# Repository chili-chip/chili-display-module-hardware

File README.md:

# chili-display-module

KiCad 10 project for the **chilichip console display module**. The module is a small board with the panel's FPC connector and backlight switch, soldered to the main board by castellated pads on its left and right edges. The panel itself is glued or screwed to the console frame, and its flex tail plugs into the module.

The console has one screen: the 2.0" IPS TFT, 320 × 240, mounted sideways. The 1.5" OLED and 1.44" TFT modules were dropped on 2026-11-27 (they are in the git history up to [#2](https://github.com/chili-chip/chili-display-module-hardware/pull/2)).

All parts are on the module's top side, so its bottom is flat. The module lies flat on the main board and is hand soldered by its edge pads, like a Raspberry Pi Pico.

Status: **schematic and PCB done, autorouted.** 28 × 22 mm. ERC and DRC are clean (DRC with schematic parity). Not ordered or tested.

| Folder | Panel | Controller | Extra parts on the module |
|---|---|---|---|
| [`tft/`](tft/) | [EastRising ER-TFT020-3](https://www.buydisplay.com/2-inch-240x320-ips-tft-lcd-display-with-connector-fpc), 2.0" IPS 320 × 240, 14-pin 0.5 mm FPC | ST7789 | Backlight switch |

| Top | Bottom |
|:---:|:---:|
|  |  |

## Board

| | |
|---|---|
| Outline | 28 × 22 mm, 1.6 mm FR-4, two layers |
| Edge pads | 8 castellated half-holes, 2.54 mm pitch, 1 mm drill: 4 on the left edge (J1), 4 on the right edge (J3) |
| Panel | Not on the module. It is mounted on the frame; its FPC tail folds back under the panel and plugs into J2 |
| Parts side | Top. The bottom is flat and lies on the main board. One-sided JLCPCB assembly |
| FPC connector | J2, Hirose FH12-14S (0.5 mm, 0.3 mm FPC), top side, opening at the bottom edge, centred at x = 8.5 mm (off centre, see below) |
| GND | Poured on both layers |
| Test pads | 8 bare 1 mm pads on the top side, labelled on the silkscreen (see below). No assembly needed |

Coordinates are top view, origin at the module's top-left corner.

### Edge pads

| Pad | Edge, y (mm) | Net | RP2350 GPIO |
|---|---|---|---|
| J1.1 | Left, 14.81 | 3V3 | |
| J1.2 | Left, 12.27 | GND | |
| J1.3 | Left, 9.73 | `DISP_DIN` | GP27 |
| J1.4 | Left, 7.19 | `DISP_CLK` | GP26 |
| J3.1 | Right, 7.19 | `DISP_CS` | GP28 |
| J3.2 | Right, 9.73 | `DISP_DC` | GP22 |
| J3.3 | Right, 12.27 | `DISP_RST` | GP21 |
| J3.4 | Right, 14.81 | GND | |

The signals and GPIOs are the same as the old Waveshare module, so the firmware pin map doesn't change.

### Test pads

8 test pads on the top side, for probing during bring-up before the panel goes on. They are bare copper, so they add no parts and no cost.

| Pad | Net |
|---|---|
| TP1 | 3V3 |
| TP2 | GND |
| TP3 | `DISP_DIN` |
| TP4 | `DISP_CLK` |
| TP5 | `DISP_CS` |
| TP6 | `DISP_DC` |
| TP7 | `DISP_RST` |
| TP8 | BL: backlight cathode (`LED_K`) |

### Main board footprint

[`chili-display-module.pretty/ChiliDisplayModule_Host.kicad_mod`](chili-display-module.pretty/ChiliDisplayModule_Host.kicad_mod) is the footprint for the main board. It has the 8 pads (numbered 1–8 in the order of the table above) and the module outline on the silkscreen.

```
      0                                28   (mm)
   0  +---------------------------------+   module outline
      |                                 |
     pad                               pad
     pad   keep parts and bare copper  pad   pads stick out 1.6 mm
     pad   out from under the module   pad   past each side edge
     pad                               pad
      |                                 |
  22  +---------------------------------+
```

| | |
|---|---|
| Host pads | 2.6 × 1.6 mm, centred 0.3 mm outside the module edge, so the solder fillet forms on the edge |
| Under the module | No parts and no bare copper. Tracks and tented vias are fine |
| Height above the main board | 3.6 mm: 1.6 mm board plus the FH12 connector (2.0 mm), the tallest part. The panel sits on the frame above |

### Backlight follows `DISP_RST`

The console has no free GPIO, so the reset line is also the backlight switch:

| `DISP_RST` | Backlight |
|---|---|
| High (running) | On |
| Low (reset, sleep) | Off |

A 100 kΩ pull-down keeps it off while the RP2350 boots. Sleep mode must hold `DISP_RST` low ([32blit-sdk #97](https://github.com/chili-chip/32blit-sdk/issues/97)).

```mermaid
flowchart LR
    RST[DISP_RST] --> P[Panel RESET]
    RST --> Q1[Q1 AO3400A] --> BL[Backlight cathode]
```

## Parts

| Ref | Part | Value | LCSC | Why |
|---|---|---|---|---|
| J1, J3 | Castellated edge pads | | part of the board | To the main board |
| J2 | Hirose FH12-14S-0.5SH | | to pick | Panel FPC |
| C1, C2 | Decoupling | 100 nF, 4.7 µF | C1525, C19666 | VDD and IOVDD |
| R1 | Backlight resistor | 6.8 Ω | to pick | 3 LEDs in parallel: 45 mA typical, 60 mA max, Vf 3.0 V. (3.3 − 3.0 V) / 6.8 Ω ≈ 44 mA. At Vf 2.9 V it is 59 mA, still under the limit. About 13 mW, fine for 0402 |
| Q1 | AO3400A N-MOSFET | | C20917 | Switches the backlight cathode |
| R2 | Gate pull-down | 100 kΩ | C25741 | Backlight off while RST floats |

Panel pins (datasheet 4.1): 1 NC, 2 GND, 3 LED−, 4 LED+, 5 GND, 6 /RESET, 7 RS (DC), 8 SDA, 9 SCK, 10 VDD, 11 IOVDD, 12 CS, 13 GND, 14 NC. VDD (2.5–3.3 V) and IOVDD (1.8–3.3 V) both run at 3.3 V.

## Panel and mounting

| | |
|---|---|
| Outline | 47.8 × 34.6 × 2.05 mm |
| Active area | 40.8 × 30.6 mm |
| Mounting | Sideways (320 wide, 240 tall), glued or screwed to the frame |
| Tail | Leaves one short edge, off centre (centre line 13.55 mm from one long edge), about 13.5 mm long, 7.5 mm wide contact end. Turn the panel so the tail exits on the left, away from the antenna, and fold it back under the panel into J2 |
| TE pin | None |
| Brightness | 300 cd/m², not sunlight readable |

J2 is off centre (x = 8.5 mm, close to the J1 side) so the folded tail reaches it while the module's pads stay clear of the RP2350 board's USB-C slots on the main board.

Firmware: the `dbi_st7789_scaled` driver ([32blit-sdk #114](https://github.com/chili-chip/32blit-sdk/pull/114)) shows today's 128 × 128 games scaled to 240 × 240 in the middle of the panel. Full 320 × 240 for new games is [32blit-sdk #115](https://github.com/chili-chip/32blit-sdk/issues/115).

## Still to do

- [ ] Check with a real panel which way the FPC tail bends into J2 and which side its contacts face. If pin 1 ends up on the wrong side, mirror the pin order.
- [ ] Put the host footprint on the main board ([vgc-zero-hardware](https://github.com/chili-chip/vgc-zero-hardware)) and line the shell window up with the panel.
- [ ] Pick the LCSC parts marked "to pick".
- [ ] JLCPCB export, CI and release, like the other module repos.

## Build

```sh
kicad-cli sch erc tft/chili-display-tft.kicad_sch
kicad-cli pcb drc --schematic-parity tft/chili-display-tft.kicad_pcb
```

KiCad needs the standard symbol and footprint libraries. The castellated pads come from `chili-display-module.pretty`, which the project loads through its `fp-lib-table`.

When ordering at JLCPCB, set **Castellated Holes: Yes**. ENIG is recommended for the fine-pitch FPC connector.

## Licence

MIT, see [LICENSE](LICENSE).

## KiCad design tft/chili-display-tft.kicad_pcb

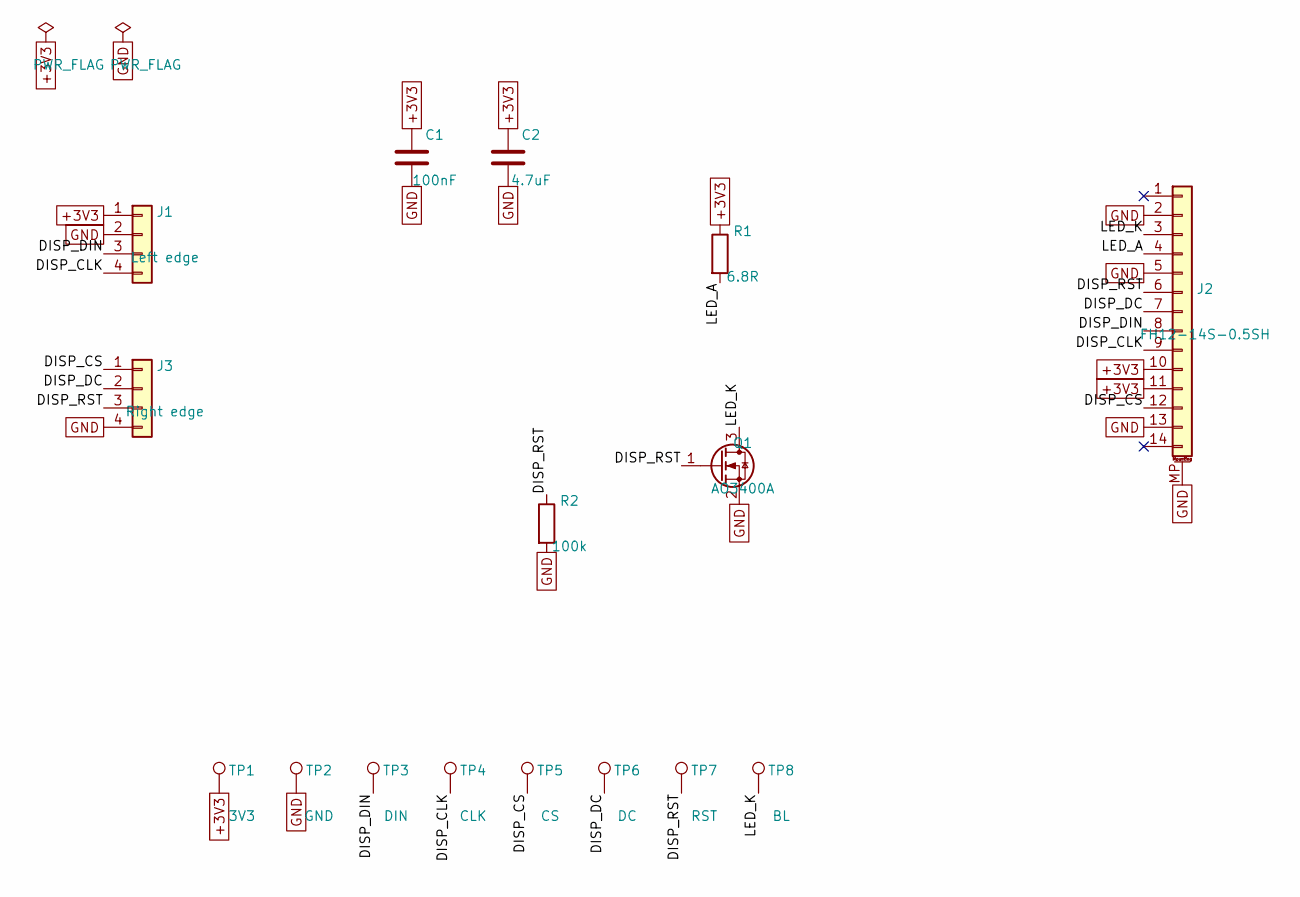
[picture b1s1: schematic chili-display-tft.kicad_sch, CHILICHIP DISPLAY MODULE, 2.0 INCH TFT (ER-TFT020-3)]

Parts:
C1: 100nF; C_0402_1005Metric; LCSC C1525
C2: 4.7uF; C_0603_1608Metric; LCSC C19666
J1: Left edge; Castellated_1x04_P2.54mm
J2: FH12-14S-0.5SH; Hirose_FH12-14S-0.5SH_1x14-1MP_P0.50mm_Horizontal
J3: Right edge; Castellated_1x04_P2.54mm
Q1: AO3400A; SOT-23; LCSC C20917
R1: 6.8R; R_0402_1005Metric
R2: 100k; R_0402_1005Metric; LCSC C25741
TP1: 3V3; TestPoint_Pad_D1.0mm
TP2: GND; TestPoint_Pad_D1.0mm
TP3: DIN; TestPoint_Pad_D1.0mm
TP4: CLK; TestPoint_Pad_D1.0mm
TP5: CS; TestPoint_Pad_D1.0mm
TP6: DC; TestPoint_Pad_D1.0mm
TP7: RST; TestPoint_Pad_D1.0mm
TP8: BL; TestPoint_Pad_D1.0mm

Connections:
+3V3: C1.1, C2.1, J1.1, J2.10, J2.11, R1.1, TP1.1
/DISP_CLK: J1.4, J2.9, TP4.1
/DISP_CS: J2.12, J3.1, TP5.1
/DISP_DC: J2.7, J3.2, TP6.1
/DISP_DIN: J1.3, J2.8, TP3.1
/DISP_RST: J2.6, J3.3, Q1.1 (G), R2.1, TP7.1
/LED_A: J2.4, R1.2
/LED_K: J2.3, Q1.3 (D), TP8.1
GND: C1.2, C2.2, J1.2, J2.2, J2.5, J2.13, J2.MP (MountPin), J3.4, Q1.2 (S), R2.2, TP2.1

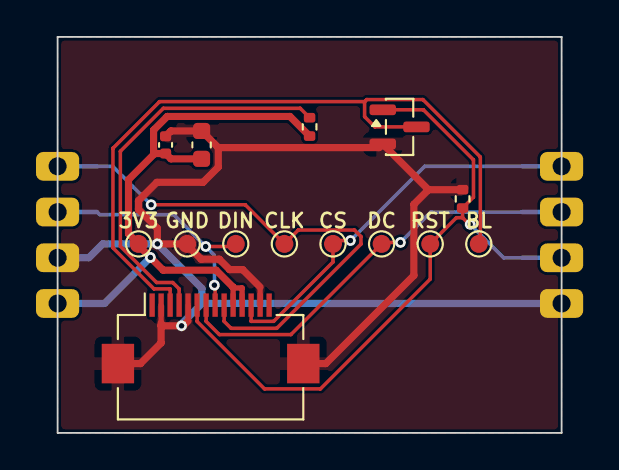
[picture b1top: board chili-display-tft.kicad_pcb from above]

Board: 2 copper layers, 28.0 x 22.0 mm, 16 parts (0 on the bottom side), 9 nets.

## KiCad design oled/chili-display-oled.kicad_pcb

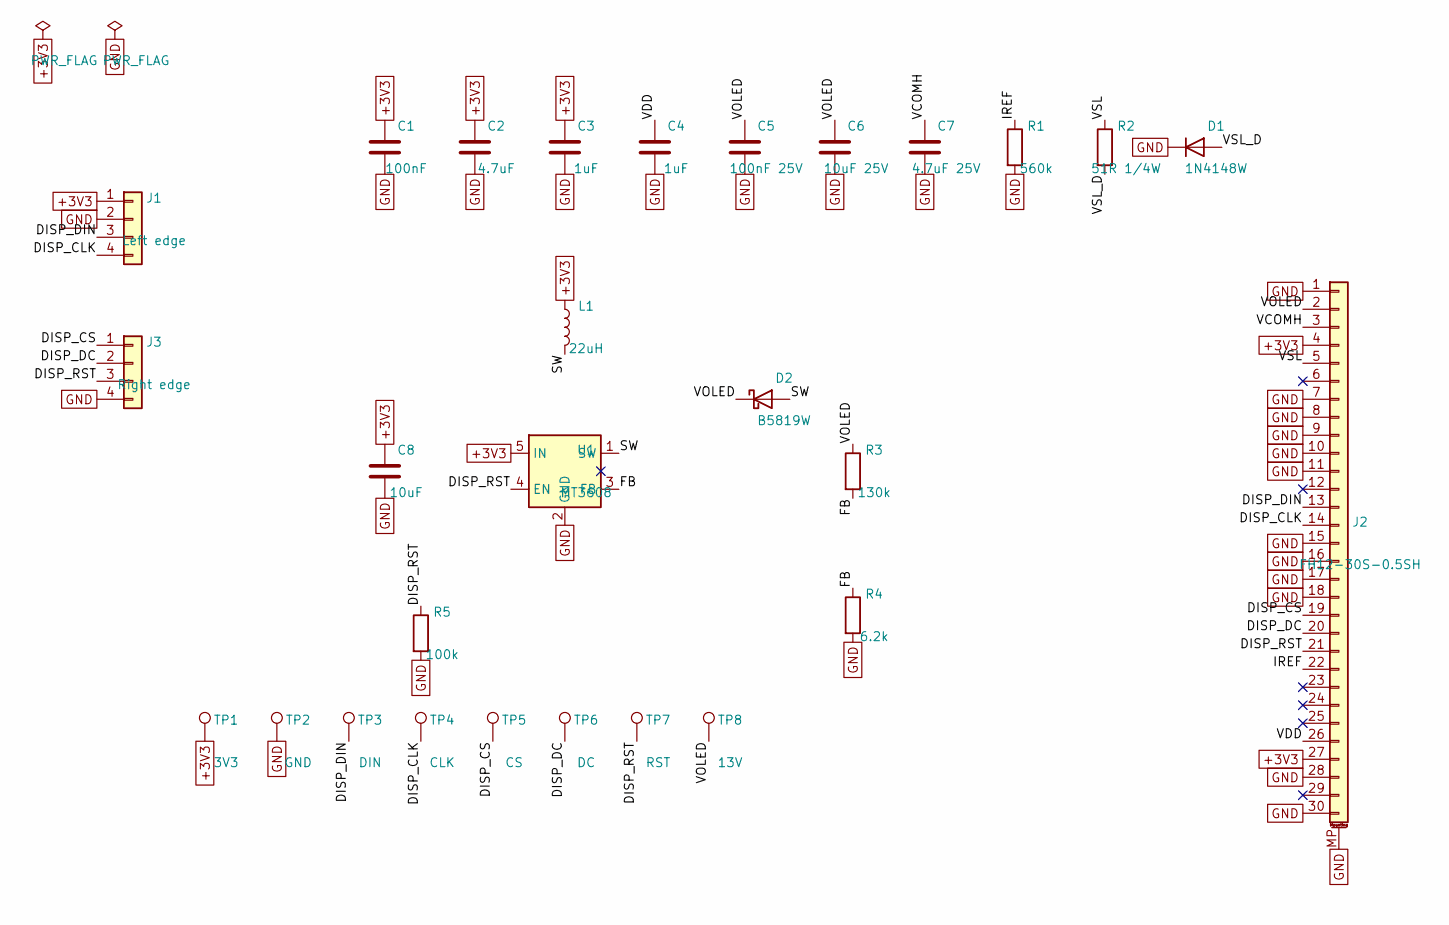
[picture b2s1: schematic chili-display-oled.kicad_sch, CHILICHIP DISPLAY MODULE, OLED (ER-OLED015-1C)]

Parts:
C1: 100nF; C_0402_1005Metric; LCSC C1525
C2: 4.7uF; C_0603_1608Metric; LCSC C19666
C3, C4: 1uF; C_0402_1005Metric; LCSC C52923
C5: 100nF 25V; C_0402_1005Metric
C6: 10uF 25V; C_0805_2012Metric
C7: 4.7uF 25V; C_0805_2012Metric
C8: 10uF; C_0603_1608Metric; LCSC C19702
D1: 1N4148W; D_SOD-123; LCSC C81598
D2: B5819W; D_SOD-123; LCSC C8598
J1: Left edge; Castellated_1x04_P2.54mm
J2: FH12-30S-0.5SH; Hirose_FH12-30S-0.5SH_1x30-1MP_P0.50mm_Horizontal
J3: Right edge; Castellated_1x04_P2.54mm
L1: 22uH; L_Sunlord_MWSA0412S
R1: 560k; R_0402_1005Metric
R2: 51R 1/4W; R_1206_3216Metric
R3: 130k; R_0402_1005Metric
R4: 6.2k; R_0402_1005Metric
R5: 100k; R_0402_1005Metric; LCSC C25741
TP1: 3V3; TestPoint_Pad_D1.0mm
TP2: GND; TestPoint_Pad_D1.0mm
TP3: DIN; TestPoint_Pad_D1.0mm
TP4: CLK; TestPoint_Pad_D1.0mm
TP5: CS; TestPoint_Pad_D1.0mm
TP6: DC; TestPoint_Pad_D1.0mm
TP7: RST; TestPoint_Pad_D1.0mm
TP8: 13V; TestPoint_Pad_D1.0mm
U1: MT3608; SOT-23-6; LCSC C84817

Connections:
+3V3: C1.1, C2.1, C3.1, C8.1, J1.1, J2.4, J2.27, L1.1, TP1.1, U1.5 (IN)
/DISP_CLK: J1.4, J2.14, TP4.1
/DISP_CS: J2.19, J3.1, TP5.1
/DISP_DC: J2.20, J3.2, TP6.1
/DISP_DIN: J1.3, J2.13, TP3.1
/DISP_RST: J2.21, J3.3, R5.1, TP7.1, U1.4 (EN)
/FB: R3.2, R4.1, U1.3 (FB)
/IREF: J2.22, R1.1
/SW: D2.2 (A), L1.2, U1.1 (SW)
/VCOMH: C7.1, J2.3
/VDD: C4.1, J2.26
/VOLED: C5.1, C6.1, D2.1 (K), J2.2, R3.1, TP8.1
/VSL: J2.5, R2.1
/VSL_D: D1.2 (A), R2.2
GND: C1.2, C2.2, C3.2, C4.2, C5.2, C6.2, C7.2, C8.2, D1.1 (K), J1.2, J2.1, J2.7, J2.8, J2.9, J2.10, J2.11, J2.15, J2.16, J2.17, J2.18, J2.28, J2.30, J2.MP (MountPin), J3.4, R1.2, R4.2, R5.2, TP2.1, U1.2 (GND)

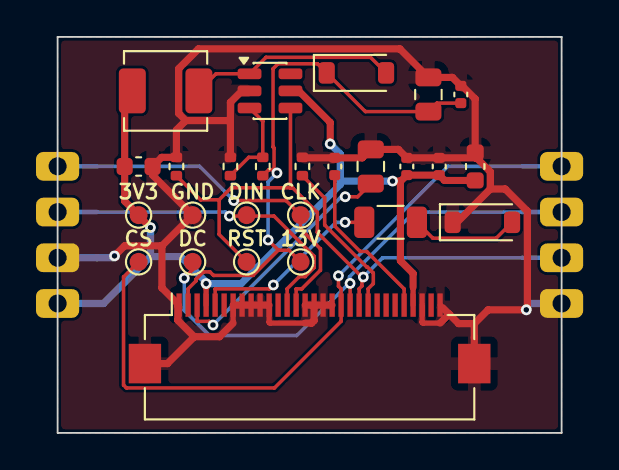
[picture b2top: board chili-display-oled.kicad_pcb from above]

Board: 2 copper layers, 28.0 x 22.0 mm, 28 parts (0 on the bottom side), 15 nets.
